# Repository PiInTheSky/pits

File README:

PITS - Tracker software for the PITS board, for use in High Altitude Ballooning.

Created by Dave Akerman (dave@daveakerman.com)

This software is written for the PITS Zero with Pi Zero, PITS+ with the various A+/B+ models, and the original PITS with the Pi A/B boards.

PITS Zero and PITS+ can be purchased from board from http://ava.upuaut.net/store/.

Software support is provided for customers who have purchased a PITS, PITS Zero or PITS+ board, for use with that board only.

INSTALLING
==========

Follow the instructions at http://www.pi-in-the-sky.com/index.php?id=sd-card-image-from-scratch

USB CAMERA
==========

To use a USB camera (i.e. a compact or SLR) instead of the Pi camera, you need to install gphoto2 and imagemagick:

	sudo apt-get install gphoto2 imagemagick

and you need to edit /boot/pisky.txt and change the "camera" line to be:

	Camera=G

(G/g are for gphoto2, U/F/u/f for fswebcam; N/n is for no camera, Y/y/1/TC/c is for CSI camera).

The camera must be able to support remote capture as well as image download, and this excludes a large number of cameras in particular all Canon compacts since 2009.
There's a list of cameras at http://www.gphoto.org/doc/remote/.

The image resolution is not controlled so you should set this up in the camera.  The full image files are stored on Pi SD card, so ensure that it has sufficient free capacity.

If you are transmitting images with SSDV, then these need to be resized before transmission.  This is configured in pisky.txt in the usual way. 
The process though is different - the camera takes the full sized image, and this image is downloaded to the Pi unaltered.  Before transmission the selected images are then resized using imagemagick.
So, regardless of the image size settings in pisky.txt, the Pi SD card will contain the full-size images.

PITS does not set the camera exposure.  Normally with the camera set to an automatic exposure mode you will get plenty of good images, but you can of course set it to any mode you wish including manual.
If you wish to control this from the software rather than on the camera, then create an executable script "take_image" (there is a sample supplied as "take_image.sample").
Note that most settings are only available in the more basic modes - e.g. the aperture can only be controlled in aperture-priority or manual modes.

gphoto2 needs more work than the other camera options, and we strongly recommend some experimentation with the camera you intend to use.  See http://gphoto.org/doc/manual/using-gphoto2.html.

USB WEBCAM
==========

To use a USB webcam instead of the Pi camera, you need to install fswebcam:

	sudo apt-get install fswebcam

and you need to edit /boot/pisky.txt and change the "camera" line to be:

	Camera=U

IMAGE PROCESSING
================

All images now include telemetry (longitude, latitude, altitude) in the JPEG comment field, but only if EXIV2 has been installed.

It is therefore possible to overlay downloaded images with telemetry data, as text or graphics, using (for example) ImageMagick, and EXIV2 to extract the data from the JPEG being processed.  A sample script is provided.  The software will automatically execute a script called "process_image" if present.

CHANGE LOG
==========

07/11/2016
==========

- Added support for USB cameras via gphoto2

19/09/2016
==========

- Red (warn) LED now flashes during wait for GPS lock; if it's on without flashing then there is no GPS data (which means GPS misconfigured, or Pi revision not recognised)

18/09/2016
==========

- Full list of Pi Zero boards
- Ignore empty CRLF lines in pisky.txt

29/09/2016
==========

- Better CPU/Pi test

25/09/2016
==========

- Added SSDV_settings to pisky.txt - add command-line parameter when calling SSDV program- Removed support for running without device tree
- Fixed setting of implicit/explicit mode manually, ditto low-data-rate optimisation
- Truncate SSDV images larger than max size (currently 4096 packets)

12/09/2016
==========

- Settable delay between packets
- Minimal "buoy mode" telemetry

14/08/2016
==========

- Added option for serial GPS connection.  Use GPS_Device=/dev/ttyACM0 for example.
- Re-enabled APRS script

12/08/2016
==========

- Fixed error where LoRa channel stopped transmitting after a few sentences if SSDV disabled on that channel
- Increased maximum size of SSDV file to 4096 packets
- Add option to disable reading of ADC, and also transmission of ADC values

17/06/2016
==========

- BME280 driver

18/05/2015
==========

- Ability to receive SMS-style messages uplinked from the ground via LoRa.  Messages are saved to a text file and can then be processed externally (e.g. by supplied Python script to display on a Pi Sense HAT)
- Ability to include, in the LoRa telemetry, CSV data from an external file.  Sample Python script supplied to build that file from Sense HAT sensor data.
- Ability to re-send SSDV packets, via LoRa, that were not received on the ground.  Uses a LoRa uplink message to define which packets need to be sent.
- Can include uplink message status in LoRa telemetry.
- Photo sizes forced to be no smaller than 320x240, to avoid limitation in raspistill program.
- RTTY can be switched off (no data no carrier) during LoRa uplink periods.
- Use of EXIV2 (if installed) to insert telemetry data into all stored JPEG images, in the JPEG comment field
- Sample image processing script to extract telemetry from JPEG comment field, and insert into downloaded images as a text overlay, using ImageMagick

01/03/2016
==========

- Test for latest Pi boards; assume PITS+ if not a known board
- clear.txt now actually works
- Better setting of MTX2 frequency

28/11/2015

- Suport for Pi Zero
- Support for USB webcam via fswebcam

12/10/2015

- Added "camera_settings" option for config file
- Fixed IP check which faulted when Pi on a VPN

18/08/2015

- Merged in LoRa code (LoRa branch is now defunct)
- Photographs can now be taken at independent rates for RTTY, LoRa, full-size
- Landing prediction option
- Fixes for multiple DS18B20 sensors
- Ability to run emulated flight from GPS NMEA file
- Ability to modify SSDV images before transmission using ImageMagick etc.
- LoRa Calling Mode
- RTTY serial port kept open continuously
- Startup radio message with IP address etc.
- Stop multiple tracker programs from being run
- Test for latest Pi board
- Option to delete existing image files at startup
- Image files now in names/dated folders e.g. /home/pi/images/RTTY/18_08_2015

17/06/2015

- Merged in APRS code (APRS branch is now defunct)
- Added options to control when APRS packets are sent
- Fixed issue with tracker program failing SD card is pulled and APRS enabled
- NTX2 frequency-setting code now has same improvements as for MTX2
- Serial port kept open now instead of open/close each packet; using flush command to sync instead of closing.  This allows ...
- ... Telemetry log entries now written whilst waiting for telemetry to Tx; removes/reduces delay due to SD card writing.

01/06/2015

- MTX2 frequency-setting code changed to fix random fails to set frequency
- logging now on by default
- log files removed from repository
- Long payload IDs are truncated to 6 before passing to SSDV program
- SSDV image widths and heights now forced to be multiples of 16 pixels
- Added support for second (external) DS18B20 temperature sensor
- Fix to occassional missing packets
- Support for Pi V2 B
- Protect against BMP085/180 being disconnected after initialisation

19/12/2014

- GPS code completely re-written to use WiringPi library instead of bcm library
- default configuration now leaves the monitor on, to ease development
- As the PITS+ boards are set by frequency in MHz, but the earlier board was
  set by channel number, the code now accepts either "frequency=nn" for channel
  number, of frequency=xxx.xxxMHz for actual frequency.  Not that using the
  second form does not give you more options on the older board - the frequency
  will be set to the closest channnel.
- Camera filenames are now the system time
- Camera images are now saved in dated folders

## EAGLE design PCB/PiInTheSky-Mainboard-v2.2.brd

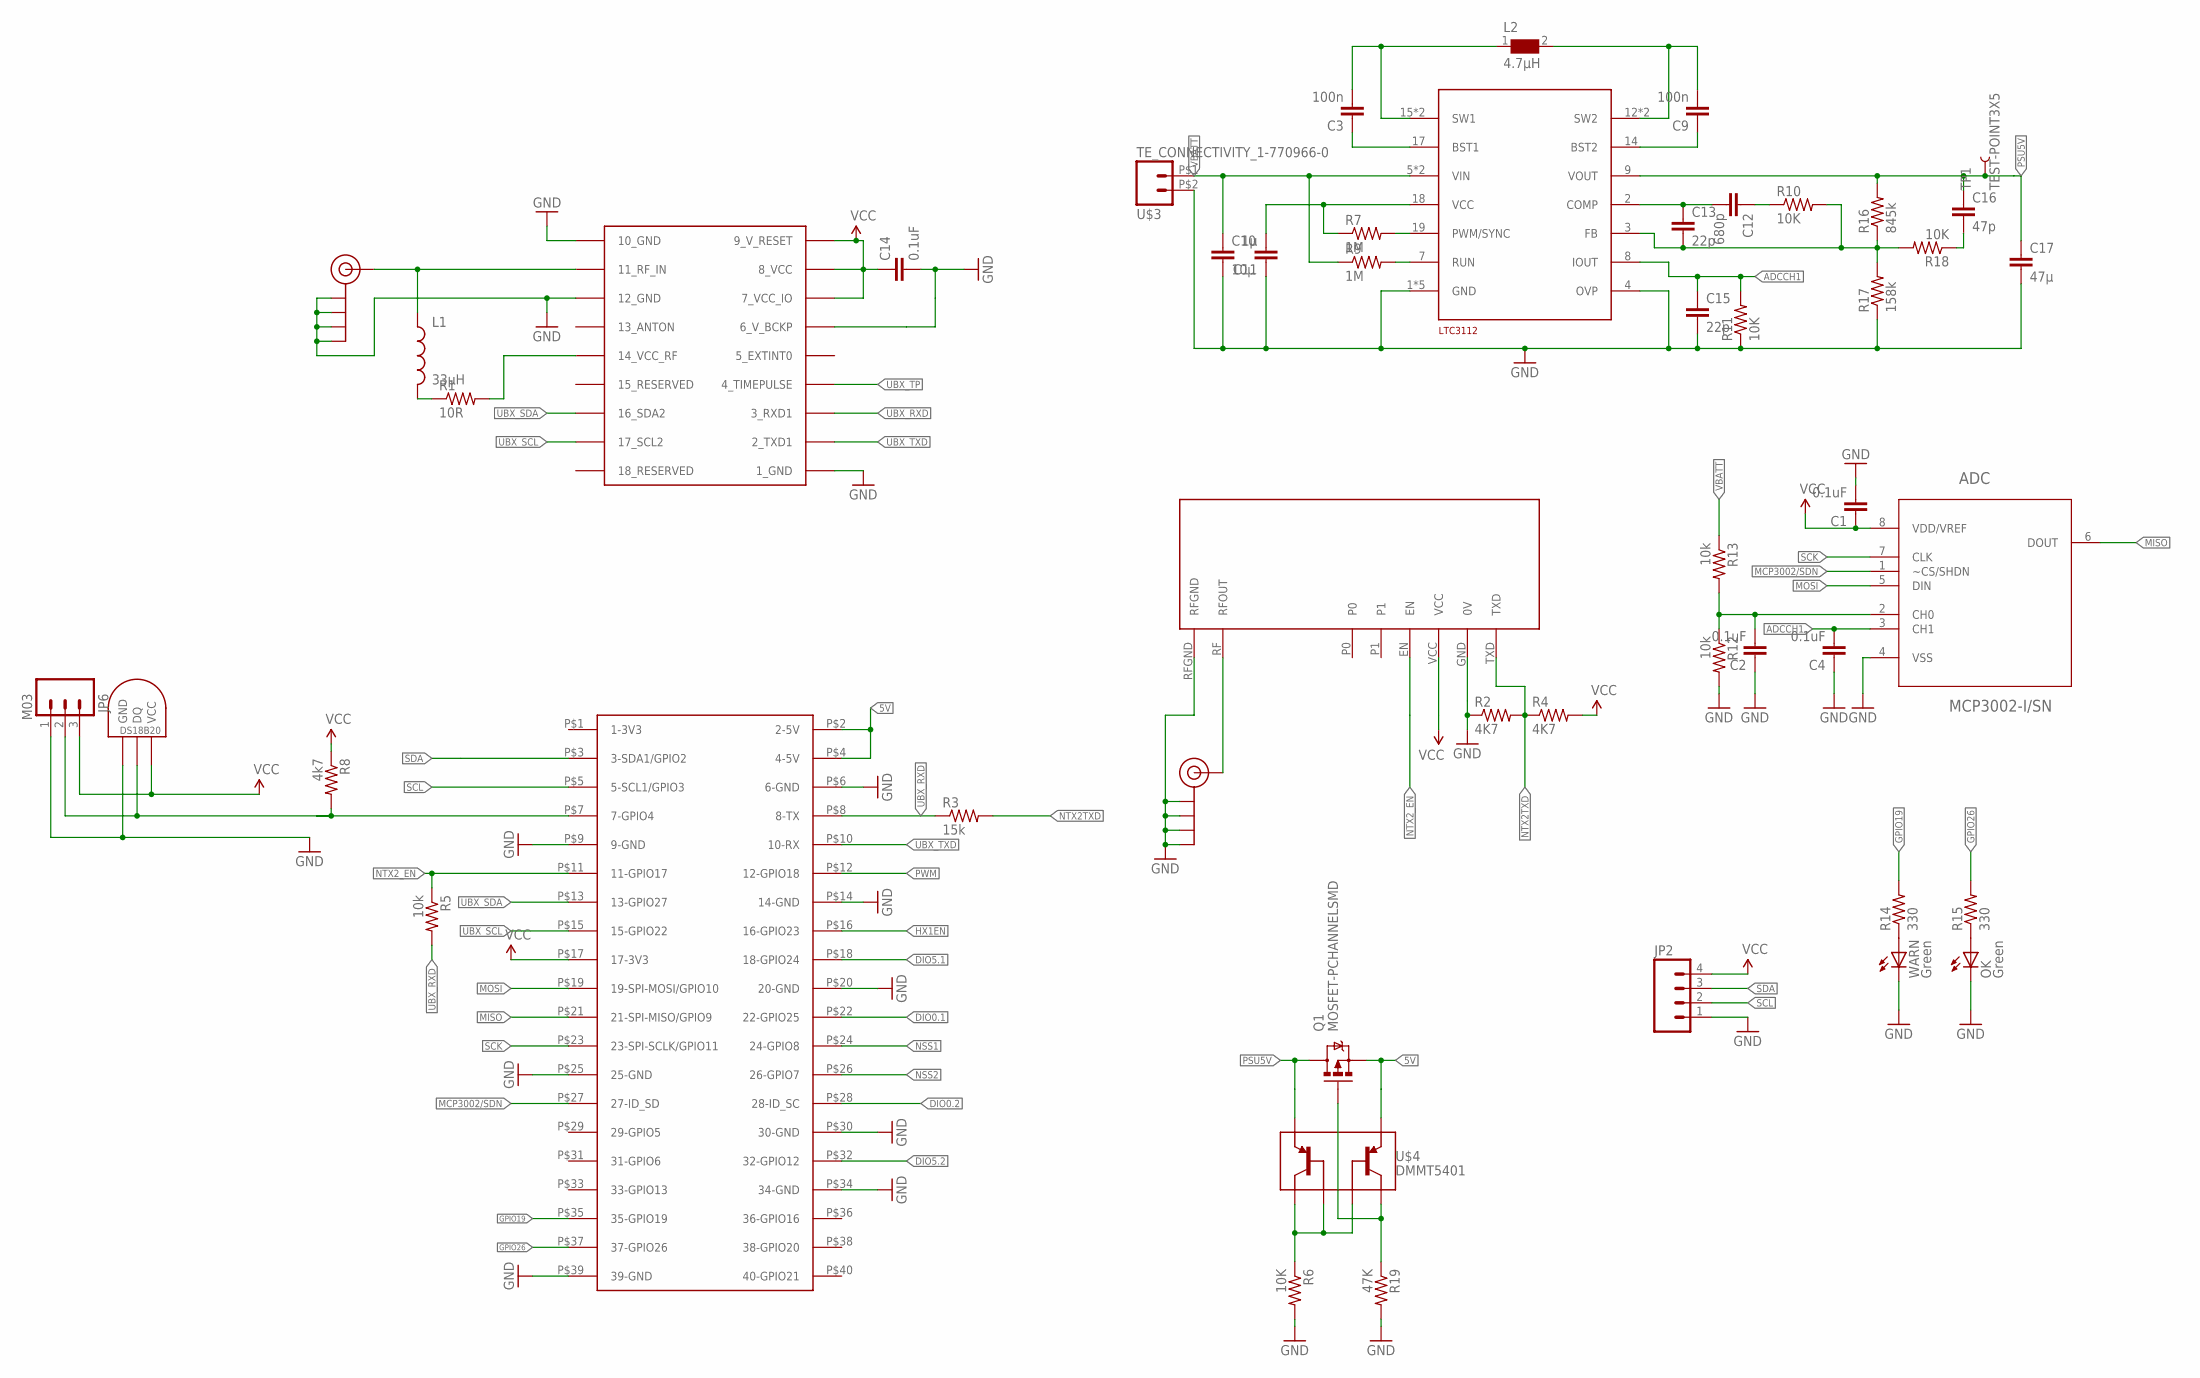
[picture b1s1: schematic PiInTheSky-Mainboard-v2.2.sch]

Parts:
ADC: MCP3002-I/SN; SOIC127P600X175-8N
C1, C2, C4, C14: 0.1uF; 0603-CAP
C3, C9: 100n; 0603-CAP
C10: 10µ; 1206
C11: 1µ; 0603-CAP
C12: 680p; 0603-CAP
C13, C15: 22p; 0603-CAP
C16: 47p; 0603-CAP
C17: 47µ; 1206
J$1, J$2: SMA_EDGE; SMA-EDGE
JP2: M04PTH; 1X04
JP6: M03; M03-JST
L1: 33µH; 0603
L2: 4.7µH; WE-HCI_7030/7040/7050
OK: Green; LED-0603
Q1: MOSFET-PCHANNELSMD; SOT23-3
R1: 10R; 0603-RES
R2, R4: 4K7; 0603-RES
R3: 15k; 0603-RES
R5, R12, R13: 10k; 0603-RES
R6, R10, R11, R18: 10K; 0603-RES
R7, R9: 1M; 0603-RES
R8: 4k7; 0603-RES
R14, R15: 330; 0603-RES
R16: 845k; 0603-RES
R17: 158k; 0603-RES
R19: 47K; 0603-RES
TEMP: DS1821; DS18B20_SOIC
TP1: TEST-POINT3X5; PAD.03X.05
U$1: RASPBERRY-PI+; RASPBERRY-PI-PLUS-CAM_NOTCH
U$3: TE_CONNECTIVITY_1-770966-0; FARNELL 1098556
U$4: DMMT5401; SOT26
U$5: LTC3112; TSSOP-20
U$7: UBLOX_MAX
U$8: RADIOMETRIX-MTX2
WARN: Green; LED-0603

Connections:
5V: Q1.2 (S), U$1.P$2 (2-5V), U$1.P$4 (4-5V), U$4.5 (E2)
ADCCH1: ADC.3 (CH1), C4.2, C15.1, R11.2, U$5.8 (IOUT)
DIO0.1: U$1.P$22 (22-GPIO25)
DIO0.2: U$1.P$28 (28-ID_SC)
DIO5.1: U$1.P$18 (18-GPIO24)
DIO5.2: U$1.P$32 (32-GPIO12)
GND: ADC.4 (VSS), C1.2, C2.1, C4.1, C10.2, C11.1, C14.2, C15.2, C17.2, J$1.GND@0 (GND), J$1.GND@1 (GND), J$1.GND@2 (GND), J$1.GND@3 (GND), J$2.GND@0 (GND), J$2.GND@1 (GND), J$2.GND@2 (GND), J$2.GND@3 (GND), JP2.1, JP6.1, OK.C, R2.1, R6.2, R11.1, R12.2, R17.1, R19.2, TEMP.GND, U$1.P$6 (6-GND), U$1.P$9 (9-GND), U$1.P$14 (14-GND), U$1.P$20 (20-GND), U$1.P$25 (25-GND), U$1.P$30 (30-GND), U$1.P$34 (34-GND), U$1.P$39 (39-GND), U$3.P$2 (2), U$5.1 (GND), U$5.4 (OVP), U$5.10 (GND), U$5.11 (GND), U$5.20 (GND), U$5.21 (GND), U$7.1_GND, U$7.6_V_BCKP, U$7.10_GND, U$7.12_GND, U$8.GND (0V), U$8.RFGND, WARN.C
GPIO1: JP6.2, R8.2, TEMP.DQ, U$1.P$7 (7-GPIO4)
GPIO19: R14.2, U$1.P$35 (35-GPIO19)
GPIO26: R15.2, U$1.P$37 (37-GPIO26)
HX1EN: U$1.P$16 (16-GPIO23)
MCP3002/SDN: ADC.1 (~CS/SHDN), U$1.P$27 (27-ID_SD)
MISO: ADC.6 (DOUT), U$1.P$21 (21-SPI-MISO/GPIO9)
MOSI: ADC.5 (DIN), U$1.P$19 (19-SPI-MOSI/GPIO10)
unnamed: J$1.SIG (SIGNAL), L1.1, U$7.11_RF_IN
unnamed: R1.2, U$7.14_VCC_RF
unnamed: L1.2, R1.1
unnamed: J$2.SIG (SIGNAL), U$8.RF (RFOUT)
unnamed: C3.1, U$5.17 (BST1)
unnamed: ADC.2 (CH0), C2.2, R12.1, R13.2
unnamed: R6.1, U$4.1 (C1), U$4.2 (B1), U$4.3 (B2)
unnamed: C9.1, U$5.14 (BST2)
unnamed: C9.2, L2.2, U$5.12 (SW2), U$5.13 (SW2)
unnamed: OK.A, R15.1
unnamed: C3.2, L2.1, U$5.15 (SW1), U$5.16 (SW1)
unnamed: C11.2, R7.1, U$5.18 (VCC)
unnamed: R9.2, U$5.7 (RUN)
unnamed: R14.1, WARN.A
unnamed: R7.2, U$5.19 (PWM/SYNC)
unnamed: C13.2, R10.2, R16.1, R17.2, R18.2, U$5.3 (FB)
unnamed: C12.2, C13.1, U$5.2 (COMP)
unnamed: C12.1, R10.1
unnamed: C16.2, R18.1
unnamed: Q1.1 (G), R19.1, U$4.4 (C2)
NSS1: U$1.P$24 (24-GPIO8)
NSS2: U$1.P$26 (26-GPIO7)
NTX2TXD: R2.2, R3.2, R4.1, U$8.TXD
NTX2_EN: R5.1, U$1.P$11 (11-GPIO17), U$8.EN
PSU5V: C16.1, C17.1, Q1.3 (D), R16.2, TP1.P$1, U$4.6 (E1), U$5.9 (VOUT)
PWM: U$1.P$12 (12-GPIO18)
SCK: ADC.7 (CLK), U$1.P$23 (23-SPI-SCLK/GPIO11)
SCL: JP2.2, U$1.P$5 (5-SCL1/GPIO3)
SDA: JP2.3, U$1.P$3 (3-SDA1/GPIO2)
UBX_RXD: R3.1, R5.2, U$1.P$8 (8-TX), U$7.3_RXD1
UBX_SCL: U$1.P$15 (15-GPIO22), U$7.17_SCL2
UBX_SDA: U$1.P$13 (13-GPIO27), U$7.16_SDA2
UBX_TP: U$7.4_TIMEPULSE
UBX_TXD: U$1.P$10 (10-RX), U$7.2_TXD1
VBATT: C10.1, R9.1, R13.1, U$3.P$1 (1), U$5.5 (VIN), U$5.6 (VIN)
VCC: ADC.8 (VDD/VREF), C1.1, C14.1, JP2.4, JP6.3, R4.2, R8.1, TEMP.VCC, U$1.P$17 (17-3V3), U$7.7_VCC_IO, U$7.8_VCC, U$7.9_V_RESET, U$8.VCC

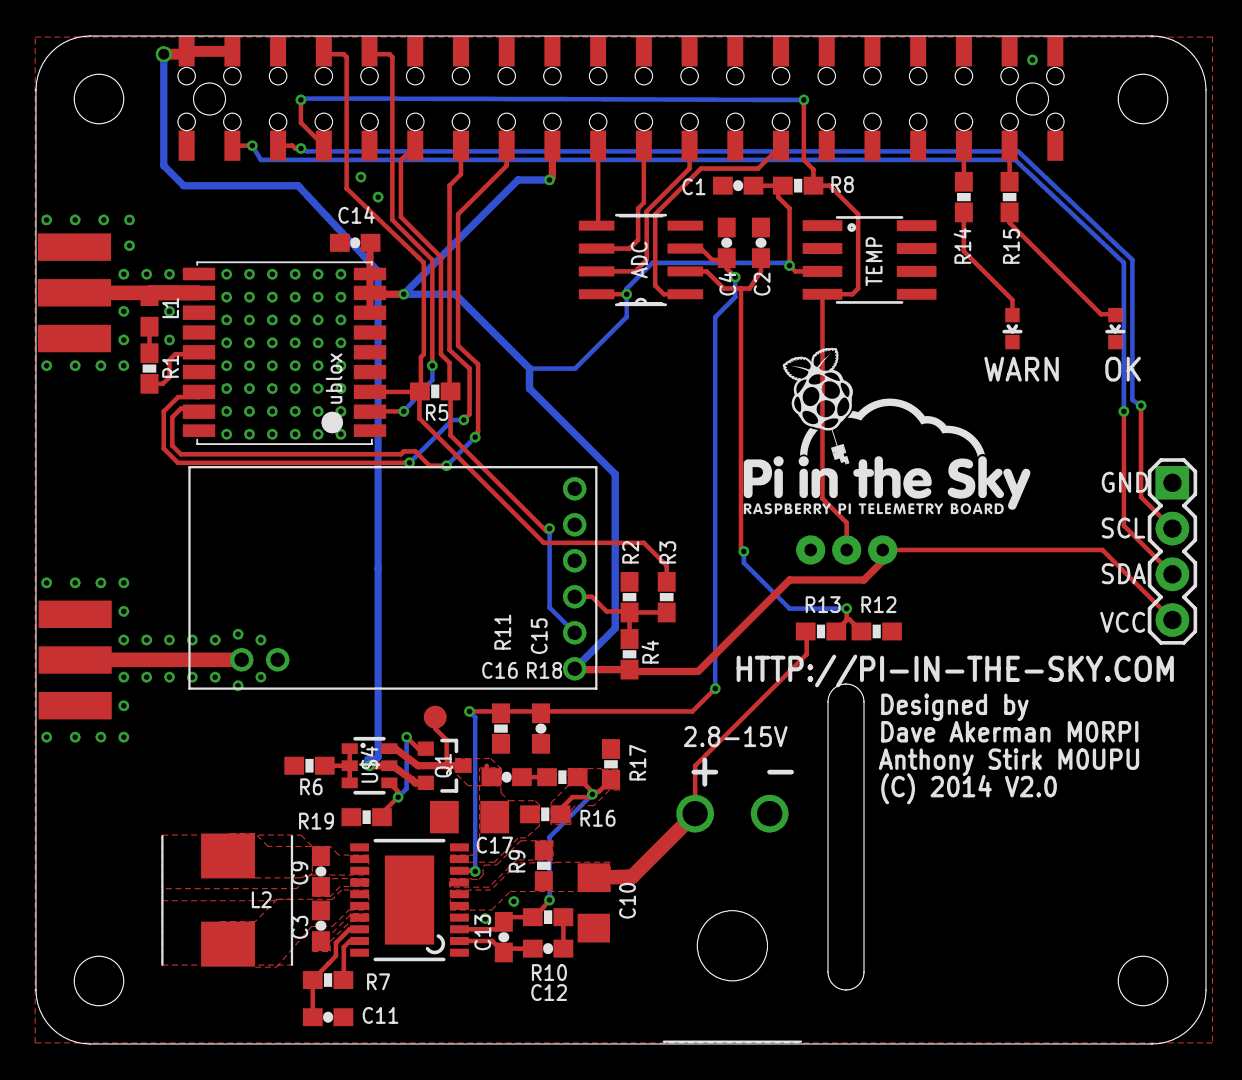
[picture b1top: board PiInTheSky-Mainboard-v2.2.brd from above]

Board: 2 copper layers, 65.0 x 56.0 mm, 52 parts (1 on the bottom side), 41 nets.

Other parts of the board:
U$2: PITS_LOGO_SMALL
U$9: NEW-HS-LOGO-MED

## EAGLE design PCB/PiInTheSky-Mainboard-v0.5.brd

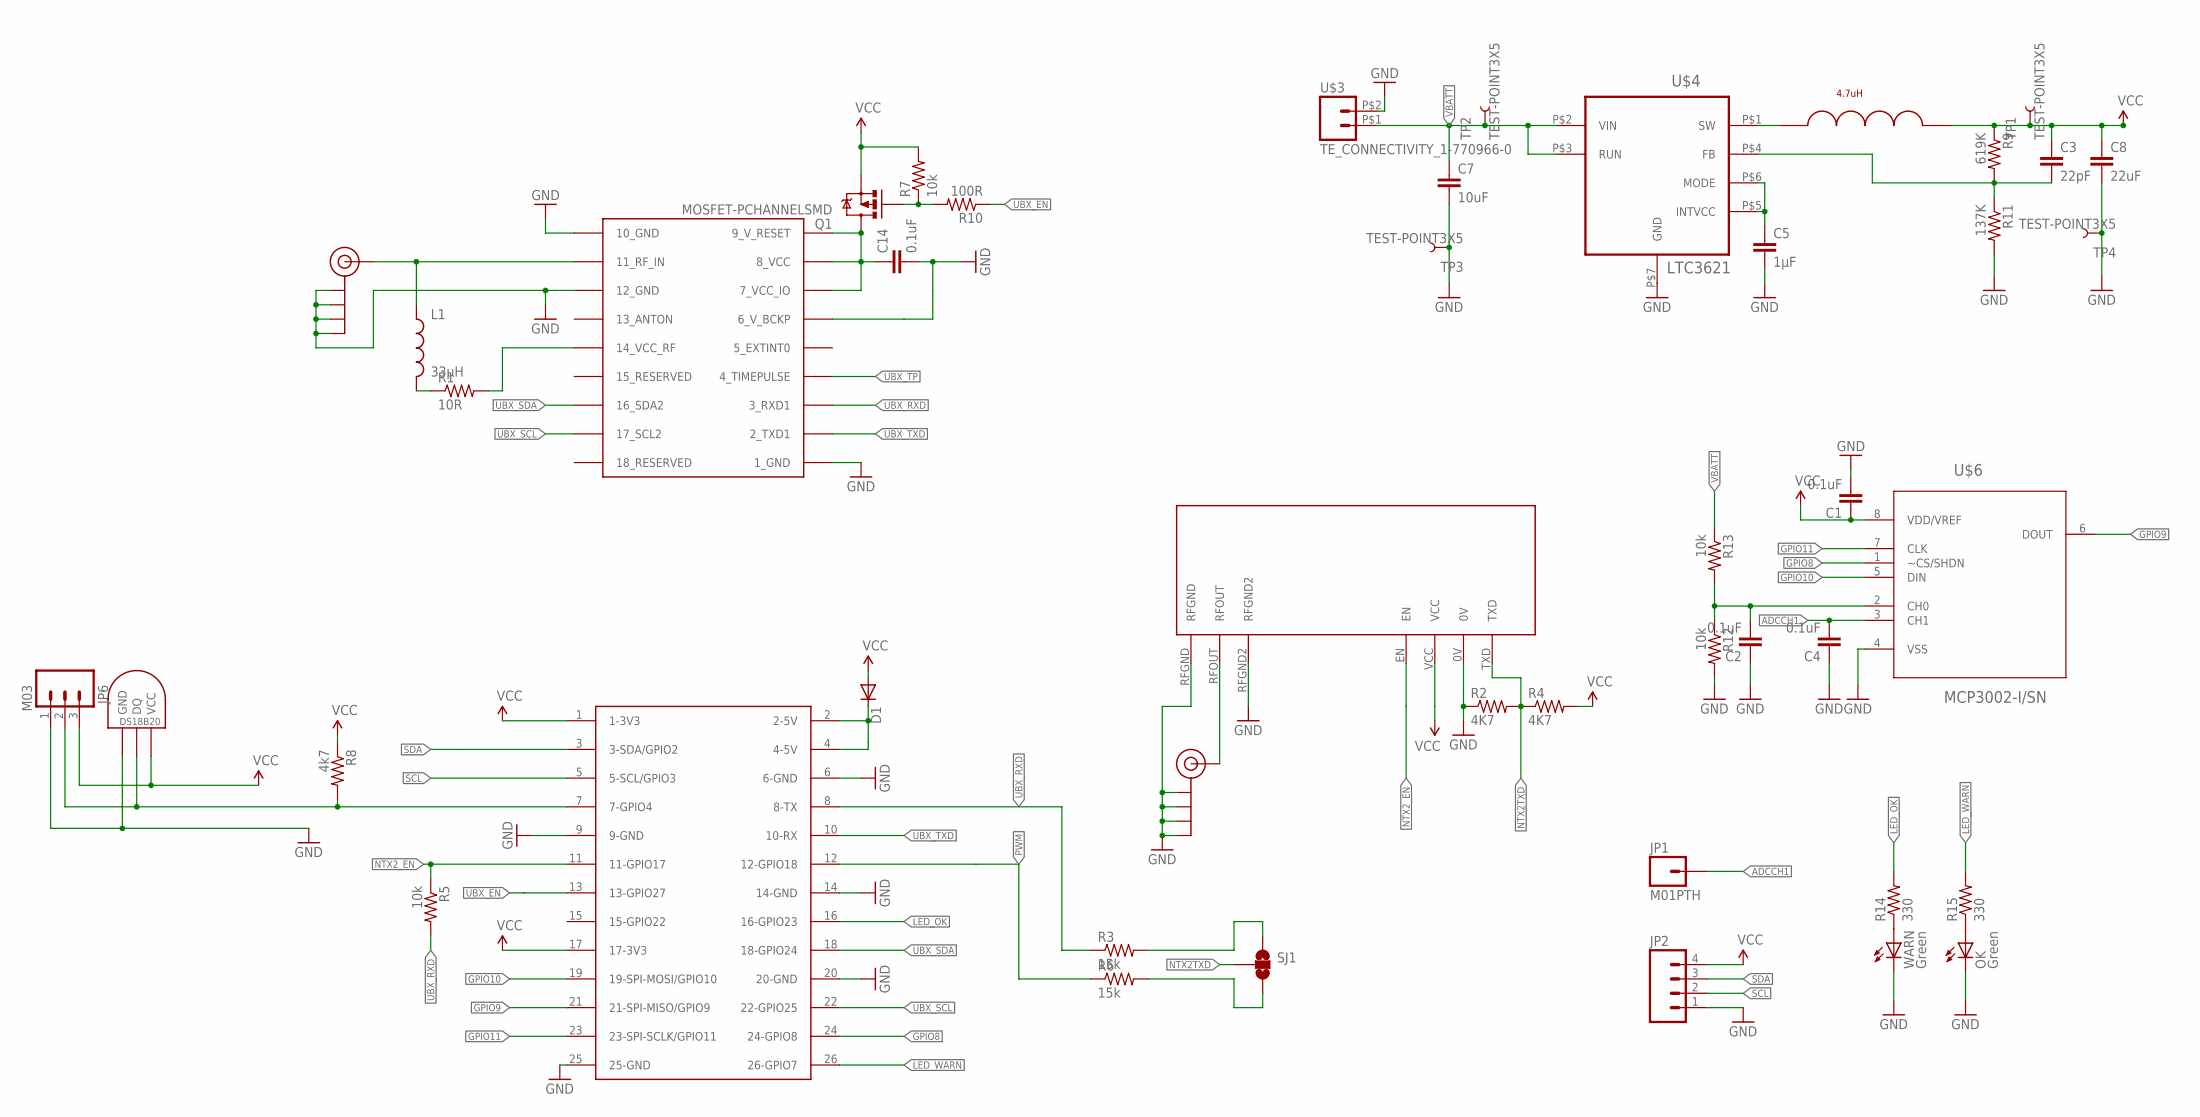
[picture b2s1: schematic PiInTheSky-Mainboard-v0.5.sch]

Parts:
C1, C2, C4, C14: 0.1uF; 0603-CAP
C3: 22pF; 0603-CAP
C5: 1µF; 0603-CAP
C7: 10uF; 1206
C8: 22uF; 1206
D1: DIODESMA; SMA-DIODE
J$1, J$2: SMA_EDGE; SMA-EDGE
JP1: M01PTH; 1X01
JP2: M04PTH; 1X04
JP6: M03; M03-JST
L1: 33µH; 0603
NTX2TEMP: DS1821; DS18B20_SOIC
OK: Green; LED-0603
Q1: MOSFET-PCHANNELSMD; SOT23-3
R1: 10R; 0603-RES
R2, R4: 4K7; 0603-RES
R3, R6: 15k; 0603-RES
R5, R7, R12, R13: 10k; 0603-RES
R8: 4k7; 0603-RES
R9: 619K; 0603-RES
R10: 100R; 0603-RES
R11: 137K; 0603-RES
R14, R15: 330; 0603-RES
SJ1: SOLDERJUMPER_2WAY-OLDPASTE2&3; SJ_3_PASTE2&3
TP1, TP2, TP3, TP4: TEST-POINT3X5; PAD.03X.05
U$1: RASPBERRY-PIRPI-HEADERONLY; RASPBERRY-PI-HEADERONLY
U$2: NTX2
U$3: TE_CONNECTIVITY_1-770966-0
U$4: LTC3621; LTC_DWG_05-08-1715_REV_A
U$5: 4.7uH; COILCRAFT_LPS4018
U$6: MCP3002-I/SN; SOIC127P600X175-8N
U$7: UBLOX_MAX-6
WARN: Green; LED-0603

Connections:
3.3V: D1.A
ADCCH1: C4.2, JP1.1, U$6.3 (CH1)
GND: C1.2, C2.1, C4.1, C5.2, C7.2, C8.2, C14.2, J$1.GND@0 (GND), J$1.GND@1 (GND), J$1.GND@2 (GND), J$1.GND@3 (GND), J$2.GND@0 (GND), J$2.GND@1 (GND), J$2.GND@2 (GND), J$2.GND@3 (GND), JP2.1, JP6.1, NTX2TEMP.GND, OK.C, R2.1, R11.2, R12.2, TP3.P$1, TP4.P$1, U$1.6 (6-GND), U$1.9 (9-GND), U$1.14 (14-GND), U$1.20 (20-GND), U$1.25 (25-GND), U$2.0V, U$2.RFGND, U$2.RFGND2, U$3.P$2 (2), U$4.P$7 (GND), U$6.4 (VSS), U$7.1_GND, U$7.6_V_BCKP, U$7.10_GND, U$7.12_GND, WARN.C
GPIO1: JP6.2, NTX2TEMP.DQ, R8.2, U$1.7 (7-GPIO4)
GPIO8: U$1.24 (24-GPIO8), U$6.1 (~CS/SHDN)
GPIO9: U$1.21 (21-SPI-MISO/GPIO9), U$6.6 (DOUT)
GPIO10: U$1.19 (19-SPI-MOSI/GPIO10), U$6.5 (DIN)
GPIO11: U$1.23 (23-SPI-SCLK/GPIO11), U$6.7 (CLK)
LED_OK: R14.2, U$1.16 (16-GPIO23)
LED_WARN: R15.2, U$1.26 (26-GPIO7)
unnamed: J$1.SIG (SIGNAL), L1.1, U$7.11_RF_IN
unnamed: R1.2, U$7.14_VCC_RF
unnamed: L1.2, R1.1
unnamed: J$2.SIG (SIGNAL), U$2.RFOUT
unnamed: U$4.P$1 (SW), U$5.P$1
unnamed: C2.2, R12.1, R13.2, U$6.2 (CH0)
unnamed: C14.1, Q1.3 (D), U$7.7_VCC_IO, U$7.8_VCC, U$7.9_V_RESET
unnamed: Q1.1 (G), R7.1, R10.2
unnamed: R3.2, SJ1.1
unnamed: C3.2, R9.2, R11.1, U$4.P$4 (FB)
unnamed: C5.1, U$4.P$5 (INTVCC), U$4.P$6 (MODE)
unnamed: OK.A, R15.1
unnamed: D1.C, U$1.2 (2-5V), U$1.4 (4-5V)
unnamed: R6.2, SJ1.3
unnamed: R14.1, WARN.A
NTX2TXD: R2.2, R4.1, SJ1.2, U$2.TXD
NTX2_EN: R5.1, U$1.11 (11-GPIO17), U$2.EN
PWM: R6.1, U$1.12 (12-GPIO18)
SCL: JP2.2, U$1.5 (5-SCL/GPIO3)
SDA: JP2.3, U$1.3 (3-SDA/GPIO2)
UBX_EN: R10.1, U$1.13 (13-GPIO27)
UBX_RXD: R3.1, R5.2, U$1.8 (8-TX), U$7.3_RXD1
UBX_SCL: U$1.22 (22-GPIO25), U$7.17_SCL2
UBX_SDA: U$1.18 (18-GPIO24), U$7.16_SDA2
UBX_TP: U$7.4_TIMEPULSE
UBX_TXD: U$1.10 (10-RX), U$7.2_TXD1
VBATT: C7.1, R13.1, TP2.P$1, U$3.P$1 (1), U$4.P$2 (VIN), U$4.P$3 (RUN)
VCC: C1.1, C3.1, C8.1, JP2.4, JP6.3, NTX2TEMP.VCC, Q1.2 (S), R4.2, R7.2, R8.1, R9.1, TP1.P$1, U$1.1 (1-3V3), U$1.17 (17-3V3), U$2.VCC, U$5.P$2, U$6.8 (VDD/VREF)

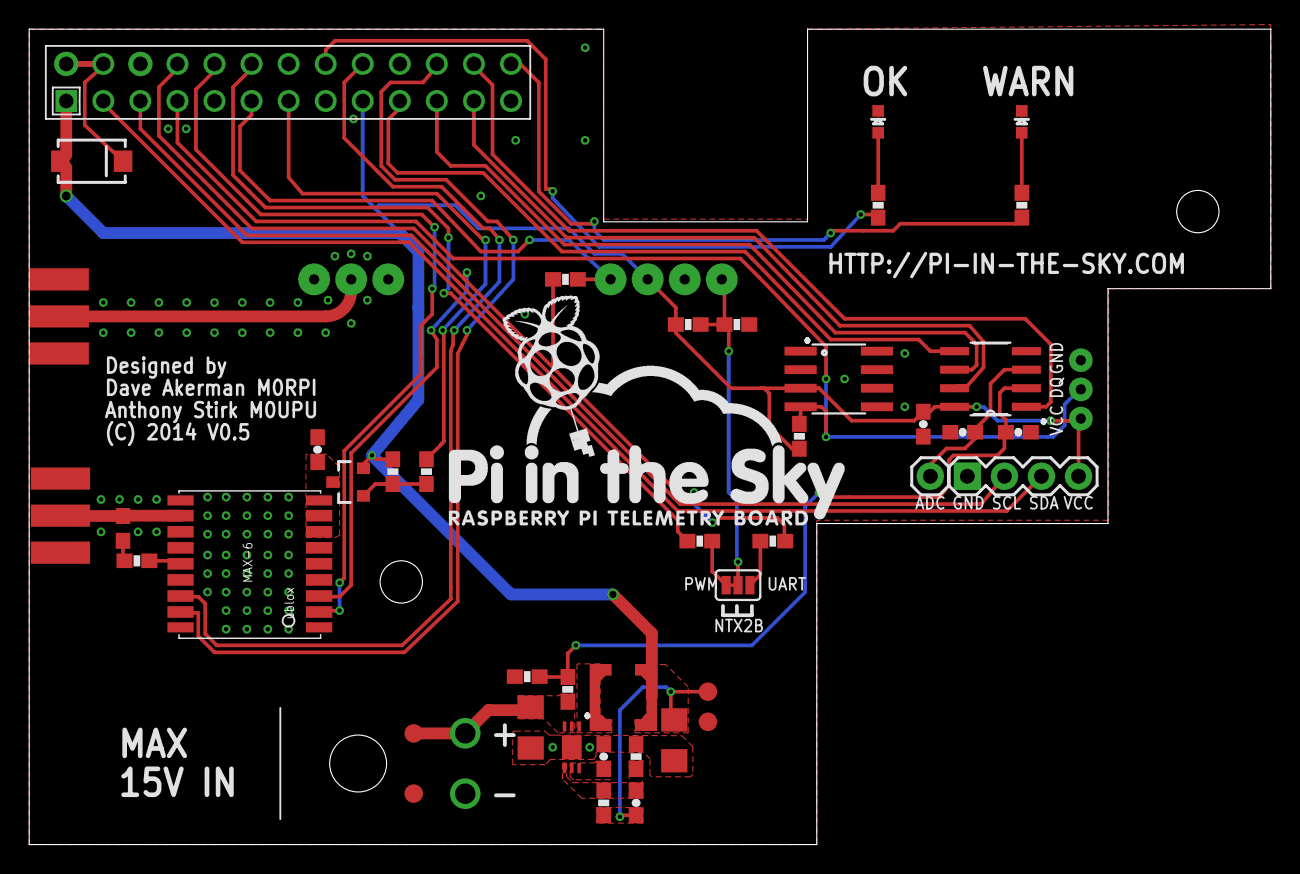
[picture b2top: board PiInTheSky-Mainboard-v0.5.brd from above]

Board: 2 copper layers, 85.1 x 55.9 mm, 47 parts (1 on the bottom side), 36 nets.

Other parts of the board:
U$8: PI_IN_SKY

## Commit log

2014-06-19 Working telemetry and SSDV
2014-06-19 Fixes to camera scripts; LEDs now have their own thread
2014-06-24 Added installer; changes for simpler installation
2014-06-26 Script toset radio frequency
2014-06-26 Tidy up
2014-06-26 Radio frequency can now be set via config file
2014-06-26 Added ability to switch off video output to save power
2014-06-27 LEDs off at altitude
2014-07-01 Fixed errors in ADC code
2014-07-01 Change telem:SSDV ratio to 1:1 at low altitudes
2014-07-01 Added support for external bmp085/180 pressure/temperature sensor
2014-07-01 Fix: corrupted sentence if BMP085 disabled
2014-07-01 Fixed error in startup script
2014-07-02 Configurable baud rate
2014-07-04 Resend flight mode less often; changed GPS parsing to remove spurious messages from RMC/GGA sentences with little data
2014-07-08 Fixed camera script (no large images)
2014-07-25 Changed LED logic so green is off when there's no lock
2014-09-09 Camera preview time extended
2014-09-28 GPS logging; Telemetry logging; Start if BMP missing but enabled; Ignore CR in config
2014-10-12 Added support for PITS B+ board
2014-10-28 Added PCB Files
    Version 2.2 PCB
    Changed PCB outline to match new HATS format (though PCB's are not HAT).
    Replaced buck/boost convertor.
    Replaced NTX2B with MTX2
2014-10-28 Wrong repo.....
2014-11-11 A+/B+ support; PITS+ V2.0 support
2014-11-11 Delay so MTX2 frequency change works on boot
2014-11-14 Disable timeout in gps i2c code
2014-11-15 Trap i2c clock error
2014-12-19 New GPS code; Freq calcs; Images by timestamp
2015-01-10 BMP085 fixes
2015-02-04 Changes for Pi 2; Fix to GPS RMC parsing
2015-04-17 Added i2c ADC support for V2.4 board
2015-06-01 Various adds and fixes - see README
2015-06-10 Fixed issue with NTX2B frequency-setting
2015-06-10 Fix to SSDV call; limit SSDV payload to 6 characters
2015-06-17 Merged in APRS code
2015-06-19 Added check for latest model B+ (Revision 0013)
2015-06-22 Send IP address and free SD space over RTTY on startup
2015-06-23 clear.txt to delete images; control of startup info messages
2015-07-03 Quick fix for temperature reading zero
2015-07-27 No more pink clouds: added -st flag to raspistill
2015-08-18 Merged LoRa branch into master
2015-09-07 Enable GPS and telemetry logging by default.
    The default pisky.txt file now has this line:
    logging=GPS,Telemetry
2015-09-07 APRS script now started by default
    The startup script now runs the APRS script. Previously this was commented out, meaning that those using APRS would have to edit the startup file.
2015-10-12 Fix to IP address check which failed if VPN present
2015-10-12 Added custom raspistill parameters to config file
2015-11-16 Now using PIGPIO for MTX2 programming
2015-11-28 Support for Pi Zero, support for fswebcam
2015-12-09 Set APRS_Random by default. Otherwise the tracker program will crash when this value is undefined.
2015-12-09 Use wiringPi to switch GPIO PWM output
2016-01-20 Correct current measurement
2016-01-30 Add correction factor due to redesign of voltage divider for voltage measurements
2016-01-30 Revert "Correct current measurement"
    This reverts commit f559743d3b01c4b0b7d05e911e843005a370d602.
2016-01-30 Add comment to explain correction factor
2016-02-07 Corrected measurements for current and voltage
2016-03-01 Full set of voards tested for; PITS+ assumed for unknown boards
2016-03-01 Full set of boards tested for; PITS+ assumed for unknown boards. Fix for MTX2 sometimes switching off during startup
2016-03-01 Fix so that creating /boot/clear.txt does actually delete image files
2016-04-06 Sense HAT telemetry; Sense HAT messaging; EXIV2 JPEG data; Telemetry overlay on SSDV
2016-04-07 Update startup
    Remove Python scripts from startup
2016-04-26 Fixed OK LED not flashing
2016-04-26 Fixed APRS for V2 Pi and OS changes
2016-05-23 Added max altitude
2016-05-24 Convert SSDV earlier; Added Pi Zero 1.3 to list
2016-06-10 Fixed telemetry bug for RTTY/LoRa
2016-06-17 BME280 Support
2016-06-21 Update misc.c
    SSDV is dropping last packet on rtty.
    (see CAENCP on ssdv.habhub.org)
2016-06-22 Fix to missing final SSDV packet in RTTY
2016-07-10 Fix to recognise Pi model A/B boards
2016-07-18 Fix to check for Pi Zero
2016-07-29 Pi V3 support
2016-08-12 Fixed LoRa stopping sending if SSDV disabled; max 4096 SSDV packets; added DisableADC option
2016-08-14 Added support for serial GPS; re-enabled APRS script
2016-08-23 first version install
2016-08-23 Update install
2016-08-24 Fixed echo messages
2016-08-24 Script checks whether Bluetooth disabled before disabling again
2016-08-30 Set board current=0 on startup
2016-08-30 Disable SPI ADC on old boards if LoRa CE0 in use
2016-08-31 Shorter delay between LoRa packets if camera disabled
2016-09-03 Uplink modes/frequency settable; fix for >256 SSDV images
2016-09-12 Added settable delay between packets, minimal telem for buoy mode, dos2unix on source
2016-09-25 Added custom SSDV parameters; truncate SSDV > 4096 packets
2016-09-29 Removed some erroneous files
2016-09-29 Better CPU/Pi test
2016-10-18 Ignore empty CRLF lines in pisky.txt
2016-10-18 Full list of Pi Zero boards
2016-10-19 Flash warn LED at GPS rate (1Hz) whilst waiting for lock
2016-11-07 Add support for USB cameras via gphoto2
2016-11-07 Removed malloc() in aprs.c
2017-01-03 Removed use of wiringPi piBoardRev() function
2017-01-06 LORA CE1 incorrect details
    changed LORA CE1 configuration from
    #LORA_image_period_0=30
    #LORA_image_packets_0=20
    to
    #LORA_image_period_1=30
    #LORA_image_packets_1=20
2017-01-19 Fixed bug where LoRa does not include int temperature with one sensor and external_temperature=1
2017-02-16 Common sentence-building code so RTTY can now include landing prediction and Sense HAT data
2017-03-03 Support Pi Zero W
2017-04-10 Added support for direct upload to habitat (e.g. via 3G net connection)
2017-04-24 Pipe now includes some GPS values
2017-05-14 Added config adc_vmax to fix voltage sense on recent boards
2017-05-22 Support for private extra modules
2017-05-22 Better error messages for BME280
2017-05-22 Finished support for private extra modules
2017-05-22 LoRa uplink extensions via private extra module
2017-06-02 Calculate flight mode / more ex_ changes
2017-06-26 Corrected I2C default multiplier and channel selection
2017-08-19 systemd startup for compatibility with Raspbian Stretch
2017-08-30 Changes to support RTLS
2017-09-01 Reduce amount of stdio output when in listen-only mode
2017-09-05 Print field list on first sentence
2017-09-15 Reinstated temperature measurement for Pi Zero/Zero W
2017-09-20 Added license file - GPL V2
2017-09-21 Added LoRa mode 8 for SSDV repeater network
2018-02-04 APRS pre-emphasis fixed
2018-02-21 More support for extension modules
2018-05-09 Added basic HABPack support, LoRa only
2018-06-03 Support for Python camera script
2018-06-03 Quick tidy
2018-09-07 L80 support
2018-09-26 Added support for RTTY via LoRa module
2018-09-27 Tidy
2018-11-21 Minor updates
2018-11-21 Added support for MS5611 pressure/temperature sensor
2018-11-22 Added support for V1 and V2 Strobon LEDs
2018-11-22 Support for Strobon LEDs
2018-11-22 Added piezo buzzer support
2018-11-30 SSDV Uplink fixes; LoRa RTTY fix
2018-12-04 Added take_photo.sample as documented for gphoto2 usage
2018-12-06 Minor change to MS5611 to work on old compilers
2019-01-23 Fixed calling mode
2019-05-09 Cache writes to log files
2019-05-09 Send prediction payload before actual payload
2019-07-07 Fixed CRC check for replaying GPS file
2019-07-08 Fix warnings from gcc in Raspbian Buster
2019-07-14 Fixed AV for cold start GPS when replaying NMEA file
2019-07-23 Fixed startup error where all logging disabled; fixed error in LoRa RST control
2019-08-27 UBlox pedestrian mode
2020-02-02 Add files via upload
    RTTY via LoRa when descending below Piezo_Alt altitude.
2020-02-02 Cutdown/Startup buzzer
    Added cutdown servo routine to trigger at specific altitude/latitude/longitude.
    Buzzer now beeps one time after Pi successfully boots.
2020-02-02 RTTY on landing
    RTTY via LoRa when descending below Piezo_Alt altitude.
2020-02-14 No null packets in mode 0 for missing camera
2020-02-23 Periodic beeping when landing
    Periodic beeping when landing, once every 10 GPS messages.
2020-03-02 Fixed bug where GPU temperature only read once
2021-01-04 Cutdown with uplink
2021-01-21 Extend uplink options
2021-02-28 Add SuperHigh functionality for all image types.
2021-04-20 Fixed SSDV wraparound of image number
2021-06-06 Fixed bug that killed RTTY if no cutdown pin configured
2021-10-14 Add LoRa calling mode options
2021-10-14 Link to LoRa calling mode
2022-05-06 Updates to replace depracated stime, and remove errors in gcc 7
2022-08-04 First commit to add EnableADCVolt option
2022-08-04 Main commit to add EnableADCVolt option
2022-08-04 Pre Test commit to add EnableADCVolt option
2022-08-04 Final commit to add EnableADCVolt option
2022-08-04 Added GPS example flight files for use by gps_source= option
2022-08-04 Added MOTD, changed startup to rc.local and Screen
2022-08-04 Added boot/pisky.current.txt as link to /boot/pisky.txt
2022-08-04 Added boot/pisky.documented.txt aligned with original pisky.txt
2022-08-04 Updated README for all commits so far
2022-08-06 Adding boot cmdline.txt and config.txt files
2022-08-15 Add logging for the camera script to camera.txt
2022-08-15 Changed links to copies of files in /boot
2022-08-16 Adding Git pre-commit
2022-08-21 Revert "Add Enable_ADC_Volt to force enabling the ADC."
2022-09-21 Added fieldlist option
2022-10-10 V1.9.1 - Support for external camera
2024-06-10 Added support for new Pi camera software

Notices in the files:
PCB/PiInTheSky-Mainboard-v0.5.brd:
(C) 2014 V0.5
PCB/PiInTheSky-Mainboard-v2.2.brd:
(C) 2014 V2.0
